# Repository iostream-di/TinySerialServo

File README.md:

# TinySerialServo
Breakout board that drives a servo via I2C, with up to 16 selectable addresses.

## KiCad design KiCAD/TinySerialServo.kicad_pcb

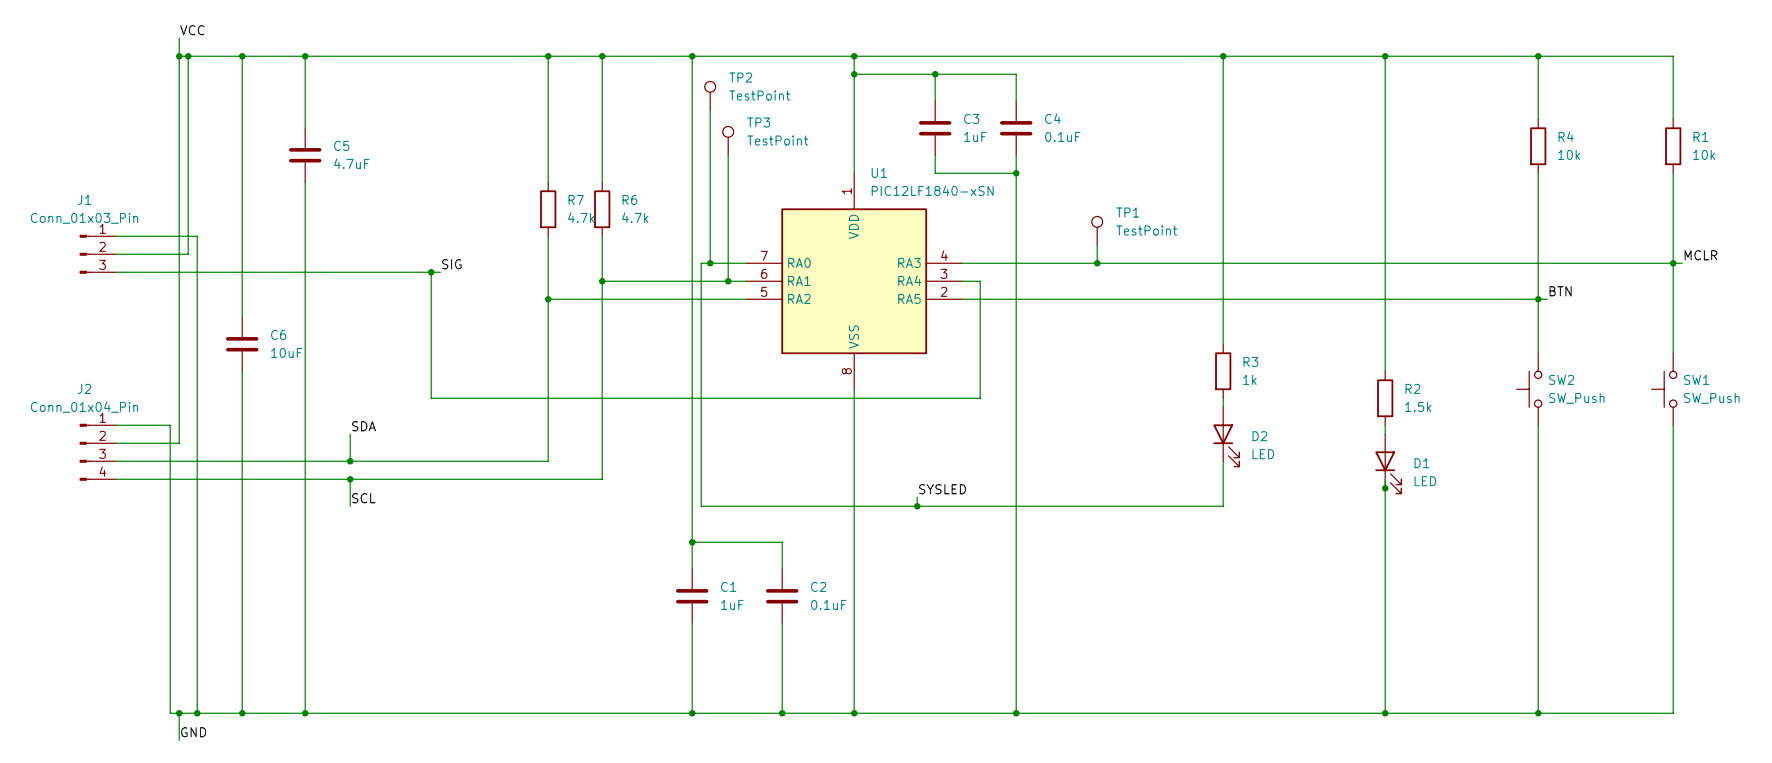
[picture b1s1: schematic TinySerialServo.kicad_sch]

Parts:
C1, C3: 1uF; C_0805_2012Metric_Pad1.18x1.45mm_HandSolder
C2, C4: 0.1uF; C_0805_2012Metric_Pad1.18x1.45mm_HandSolder
C5: 4.7uF; C_0805_2012Metric_Pad1.18x1.45mm_HandSolder
C6: 10uF; C_0805_2012Metric_Pad1.18x1.45mm_HandSolder
D1, D2: LED; LED_0805_2012Metric
J1: Conn_01x03_Pin; PinHeader_1x03_P2.54mm_Vertical
J2: Conn_01x04_Pin; PinHeader_1x04_P2.54mm_Vertical
R1, R4: 10k; R_0805_2012Metric_Pad1.20x1.40mm_HandSolder
R2: 1.5k; R_0805_2012Metric_Pad1.20x1.40mm_HandSolder
R3: 1k; R_0805_2012Metric_Pad1.20x1.40mm_HandSolder
R6, R7: 4.7k; R_0805_2012Metric_Pad1.20x1.40mm_HandSolder
SW1, SW2: SW_Push; SW_SPST_B3U-1000P
TP1, TP2, TP3: TestPoint; TestPoint_Pad_1.0x1.0mm
U1: PIC12LF1840-xSN; SOIC-8_3.9x4.9mm_P1.27mm

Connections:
/BTN: R4.2, SW2.2, U1.2 (RA5)
/GND: C1.2, C2.2, C3.2, C4.2, C5.2, C6.2, D1.1 (K), J1.1, J2.1, SW1.1, SW2.1, U1.8 (VSS)
/MCLR: R1.2, SW1.2, TP1.1, U1.4 (RA3)
/SCL: J2.4, R6.2, TP3.1, U1.6 (RA1)
/SDA: J2.3, R7.2, U1.5 (RA2)
/SIG: J1.3, U1.3 (RA4)
/SYSLED: D2.1 (K), TP2.1, U1.7 (RA0); also elsewhere on the board
/VCC: C1.1, C2.1, C3.1, C4.1, C5.1, C6.1, J1.2, J2.2, R1.1, R2.1, R3.1, R4.1, R6.1, R7.1, U1.1 (VDD)
unnamed: D1.2 (A), R2.2
unnamed: D2.2 (A), R3.2

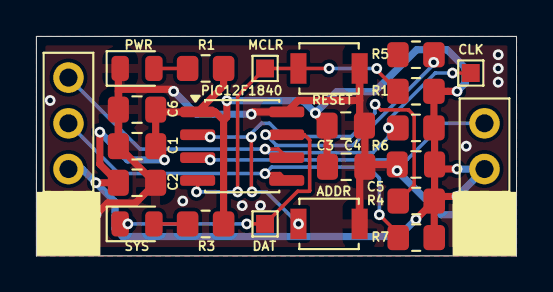
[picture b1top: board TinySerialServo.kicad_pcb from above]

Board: 2 copper layers, 26.7 x 12.2 mm, 23 parts (0 on the bottom side), 10 nets.

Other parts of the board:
R5: R; R_0805_2012Metric_Pad1.20x1.40mm_HandSolder

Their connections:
/SYSLED: R5.2; also elsewhere on the board

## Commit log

2025-12-16 Added the MPLABX project.
2025-12-16 Added the Proteus 8 project.
2025-12-16 Added the PIC12F1840 datasheet.
2025-12-17 Removed the NPN; Rerouted traces; Remapped pinouts; Changed board dimentions; Added graphics to board
2025-12-17 added the Proteus schematic image
2025-12-21 PCB Sent to OSH PARK
2025-12-21 pushed what I had on my desktop
